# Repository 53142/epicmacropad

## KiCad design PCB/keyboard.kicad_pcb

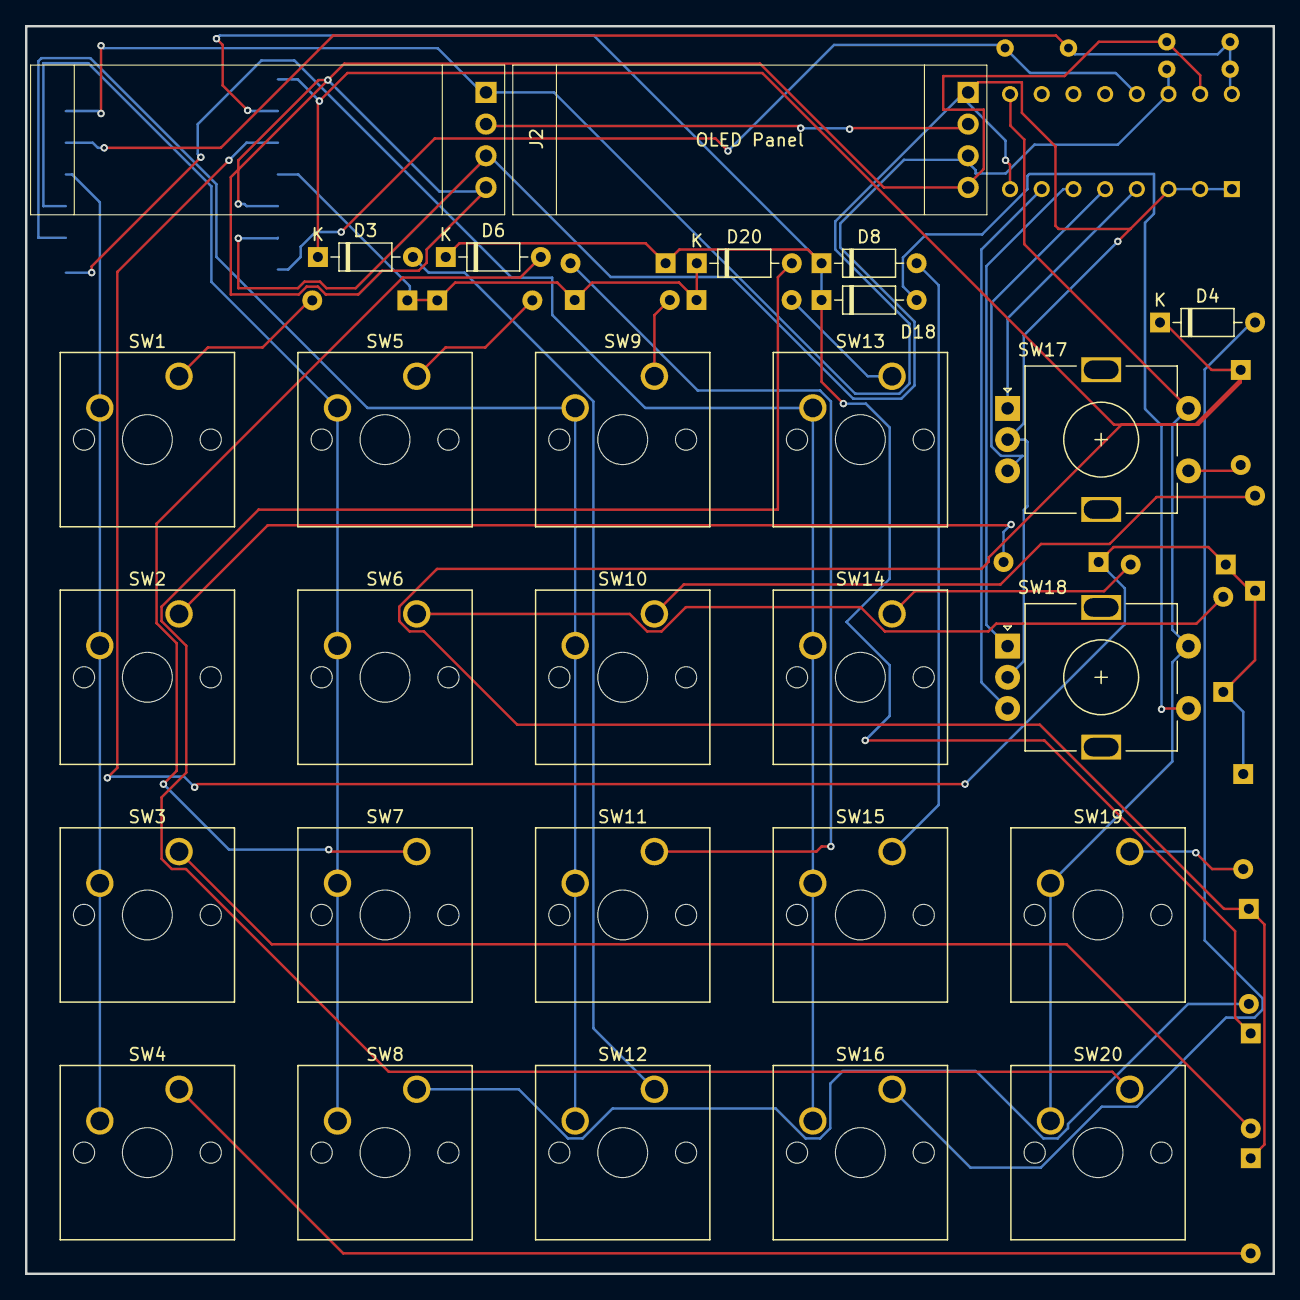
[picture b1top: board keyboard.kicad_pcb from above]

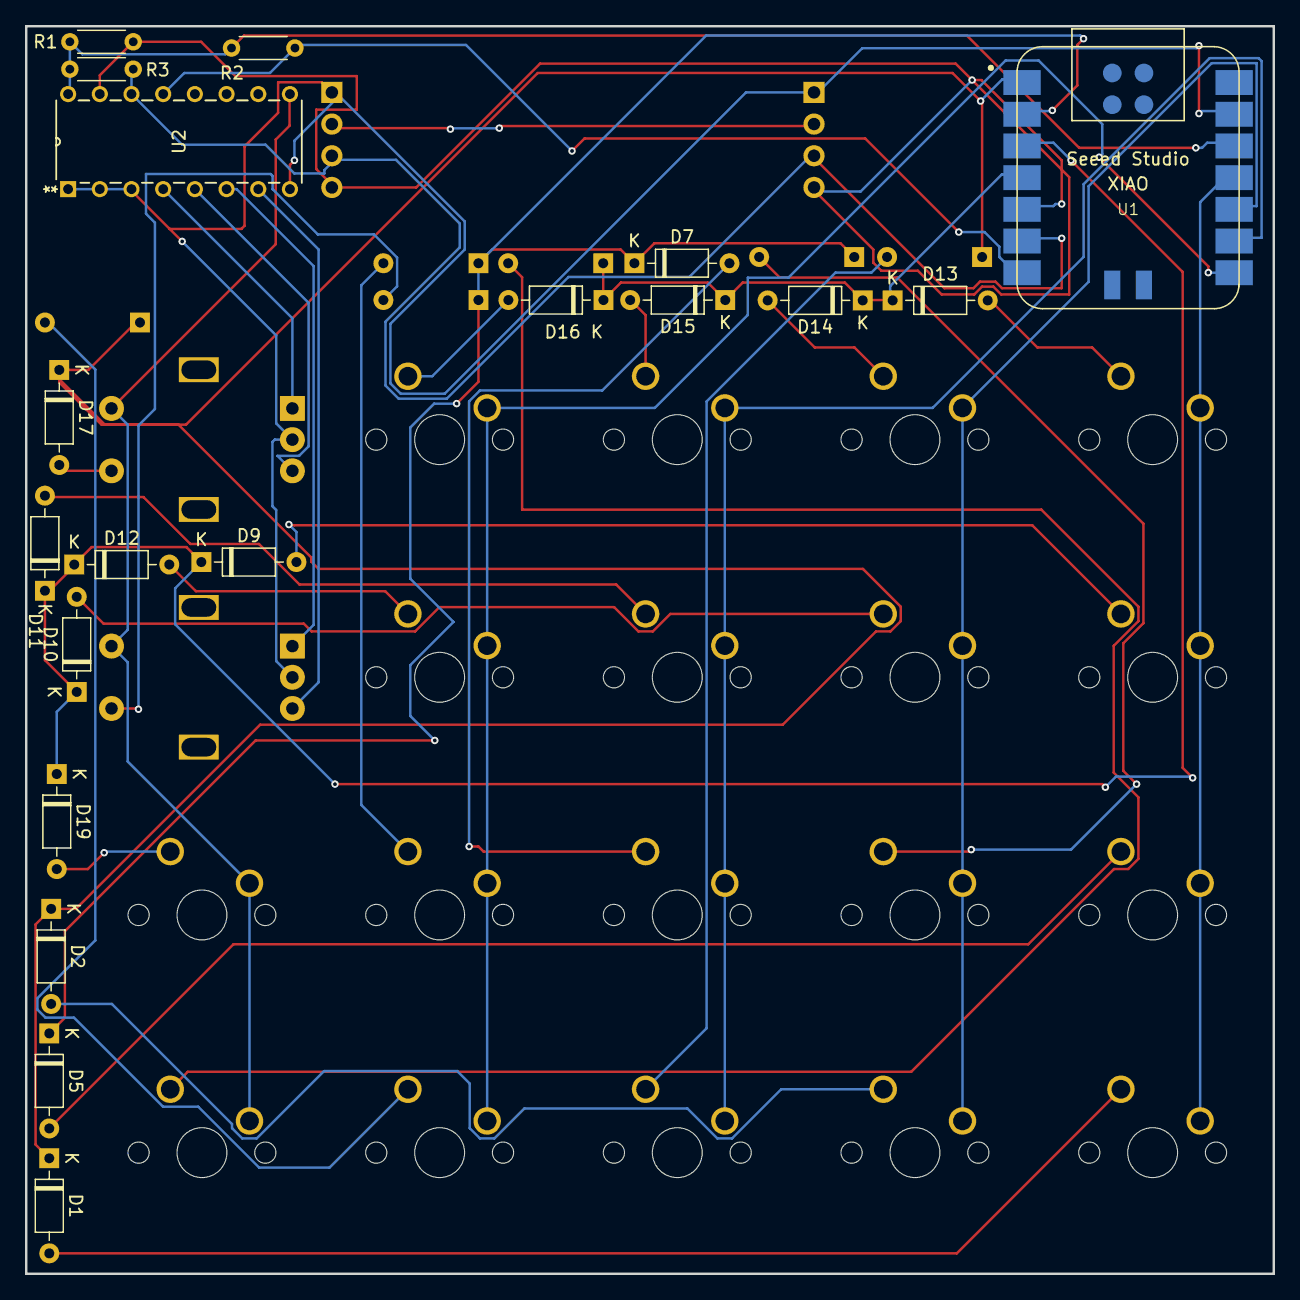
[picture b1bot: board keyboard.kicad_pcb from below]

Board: 2 copper layers, 100.0 x 100.0 mm, 47 parts (19 on the bottom side), 39 nets.

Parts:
D1, D2, D3, D4, D5, D6, D7, D8, D9, D10, D11, D12, D13, D14, D15, D16, D17, D18, D19, D20: 1N4148; D_DO-35_SOD27_P7.62mm_Horizontal
J1, J2: Conn_01x04; SSD1306-0.91-OLED-4pin-128x32
R1, R2, R3: 10k; R_Axial_DIN0204_L3.6mm_D1.6mm_P5.08mm_Horizontal
SW1, SW2, SW3, SW4, SW5, SW6, SW7, SW8, SW9, SW10, SW11, SW12, SW13, SW14, SW15, SW16, SW19, SW20: SW_Push; SW_Cherry_MX_1.00u_PCB
SW17, SW18: RotaryEncoder_Switch; RotaryEncoder_Alps_EC11E-Switch_Vertical_H20mm
U1: Seeed Studio XIAO SAMD21; XIAO-SAMD21-RP2040-14P-2.54-21X17.8MM (Seeeduino XIAO)
U2: PCF8574A

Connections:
+3V3: R1.1, R2.1, R3.2, U1.12 (3V3), U2.16 (VDD)
COL0: SW1.2, SW2.2, SW3.2, SW4.2, U1.11 (PA6_A10_D10_MOSI)
COL1: SW5.2, SW6.2, SW7.2, SW8.2, U1.10 (PA5_A9_D9_MISO)
COL2: SW9.2, SW10.2, SW11.2, SW12.2, U1.9 (PA7_A8_D8_SCK)
COL3: SW13.2, SW14.2, SW15.2, SW16.2, U1.8 (PB09_A7_D7_RX)
COL4: SW17.S2, SW18.S2, SW19.2, SW20.2, U2.9 (P4)
GND: J1.1, J2.1, SW17.C, SW18.C, U1.13 (GND), U2.1 (A0), U2.2 (A1), U2.3 (A2), U2.8 (VSS)
IO_INT: R2.2, U1.7 (PB08_A6_D6_TX), U2.13 (~INT)
unnamed: D1.2 (A), SW4.1
unnamed: D2.2 (A), SW8.1
unnamed: D3.2 (A), SW12.1
unnamed: D4.2 (A), SW16.1
unnamed: D5.2 (A), SW3.1
unnamed: D6.2 (A), SW7.1
unnamed: D7.2 (A), SW11.1
unnamed: D8.2 (A), SW15.1
unnamed: D9.2 (A), SW2.1
unnamed: D10.2 (A), SW6.1
unnamed: D11.2 (A), SW10.1
unnamed: D12.2 (A), SW14.1
unnamed: D13.2 (A), SW1.1
unnamed: D14.2 (A), SW5.1
unnamed: D15.2 (A), SW9.1
unnamed: D16.2 (A), SW13.1
unnamed: D19.2 (A), SW19.1
unnamed: D20.2 (A), SW20.1
unnamed: SW17.A, U2.4 (P0)
unnamed: SW17.B, U2.5 (P1)
unnamed: SW18.A, U2.6 (P2)
unnamed: SW18.B, U2.7 (P3)
ROW0: D1.1 (K), D2.1 (K), D3.1 (K), D4.1 (K), D17.1 (K), U1.1 (PA02_A0_D0)
ROW1: D5.1 (K), D6.1 (K), D7.1 (K), D8.1 (K), D18.1 (K), U1.2 (PA4_A1_D1)
ROW2: D9.1 (K), D10.1 (K), D11.1 (K), D12.1 (K), D19.1 (K), U1.3 (PA10_A2_D2)
ROW3: D13.1 (K), D14.1 (K), D15.1 (K), D16.1 (K), D20.1 (K), U1.4 (PA11_A3_D3)
Rotary1: D17.2 (A), SW17.S1
Rotary3: D18.2 (A), SW18.S1
SCL: J1.3, J2.3, R3.1, U1.6 (PA9_A5_D5_SCL), U2.14 (SCL)
SDA: J1.4, J2.4, R1.2, U1.5 (PA8_A4_D4_SDA), U2.15 (SDA)
VCC: J1.2, J2.2

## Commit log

2024-10-07 asdf
    asdf
2024-10-21 files
